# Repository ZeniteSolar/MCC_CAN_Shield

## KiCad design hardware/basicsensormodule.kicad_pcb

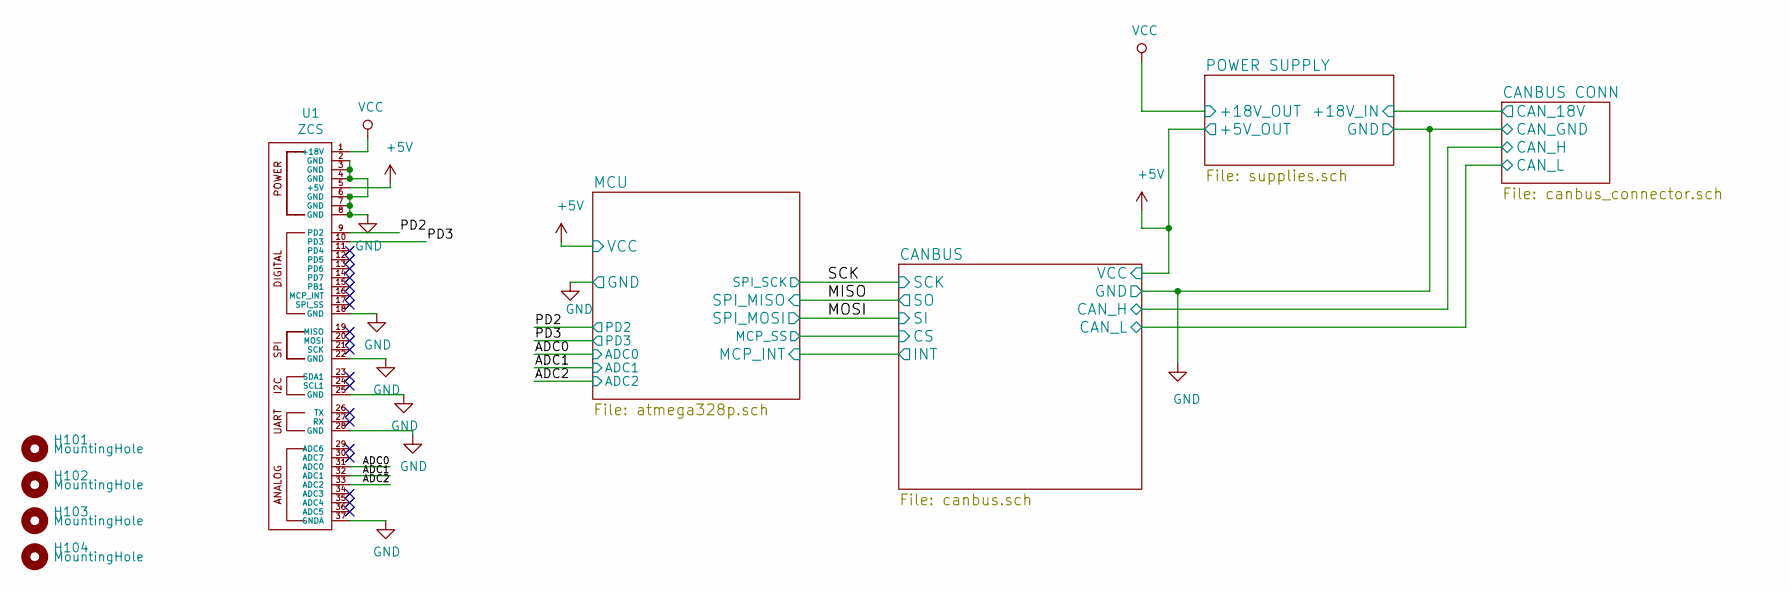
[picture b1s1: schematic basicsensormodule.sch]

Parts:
H101, H102, H103, H104: MountingHole; MountingHole_3.2mm_M3
U1: ZCS; ZCS18

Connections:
+5V: U1.5 (+5V); also elsewhere on the board
/ADC0: U1.31 (ADC0); also elsewhere on the board
/ADC1: U1.32 (ADC1); also elsewhere on the board
/ADC2: U1.33 (ADC2); also elsewhere on the board
/PD2: U1.9 (PD2); also elsewhere on the board
/PD3: U1.10 (PD3); also elsewhere on the board
GND: U1.2 (GND), U1.3 (GND), U1.4 (GND), U1.6 (GND), U1.7 (GND), U1.8 (GND), U1.18 (GND), U1.22 (GND), U1.25 (GND), U1.28 (GND), U1.37 (GNDA); also elsewhere on the board
VCC: U1.1 (+18V); also elsewhere on the board

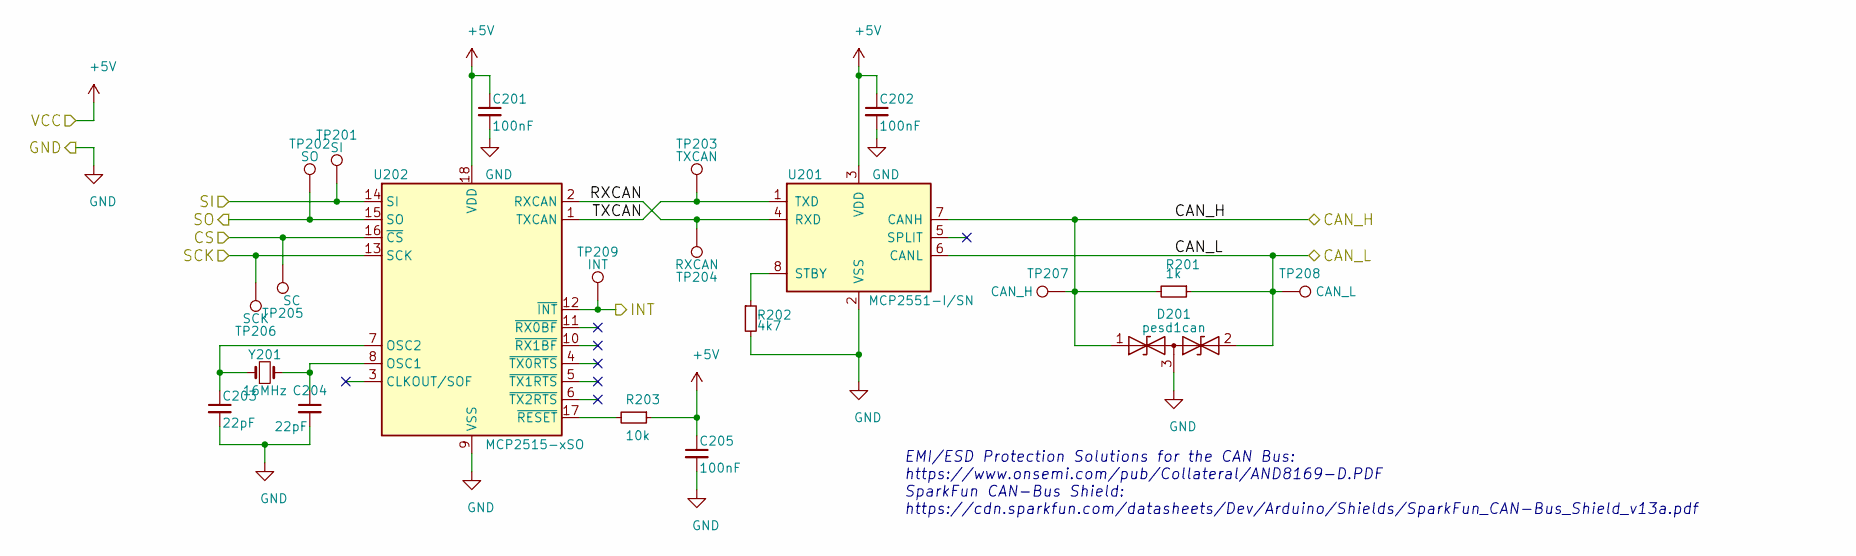
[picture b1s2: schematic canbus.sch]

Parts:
C201, C202, C205: 100nF; C_0805_2012Metric_Pad1.15x1.40mm_HandSolder
C203, C204: 22pF; C_0805_2012Metric_Pad1.15x1.40mm_HandSolder
D201: pesd1can; SOT-23_Handsoldering
R201: 1k; R_0805_2012Metric_Pad1.15x1.40mm_HandSolder
R202: 4k7; R_0805_2012Metric_Pad1.15x1.40mm_HandSolder
R203: 10k; R_0805_2012Metric_Pad1.15x1.40mm_HandSolder
TP201: SI; TestPoint_Pad_2.0x2.0mm
TP202: SO; TestPoint_Pad_2.0x2.0mm
TP203: TXCAN; TestPoint_Pad_2.0x2.0mm
TP204: RXCAN; TestPoint_Pad_2.0x2.0mm
TP205: SC; TestPoint_Pad_2.0x2.0mm
TP206: SCK; TestPoint_Pad_2.0x2.0mm
TP207: CAN_H; TestPoint_Pad_2.0x2.0mm
TP208: CAN_L; TestPoint_Pad_2.0x2.0mm
TP209: INT; TestPoint_Pad_2.0x2.0mm
U201: MCP2551-I/SN; SOIC-8_3.9x4.9mm_P1.27mm
U202: MCP2515-xSO; SOIC-18W_7.5x11.6mm_P1.27mm
Y201: 16MHz; Crystal_HC49-U_Vertical

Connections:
+5V: C201.1, C202.1, C205.1, R203.1, U201.3 (VDD), U202.18 (VDD); also elsewhere on the board
/CANBUS CONN/CAN_H: D201.1 (A1), R201.2, TP207.1, U201.7 (CANH); also elsewhere on the board
/CANBUS CONN/CAN_L: D201.2 (A2), R201.1, TP208.1, U201.6 (CANL); also elsewhere on the board
/CANBUS/CS: TP205.1, U202.16 (~CS); also elsewhere on the board
/CANBUS/INT: TP209.1, U202.12 (~INT); also elsewhere on the board
/CANBUS/RXCAN: TP204.1, U201.4 (RXD), U202.2 (RXCAN)
/CANBUS/TXCAN: TP203.1, U201.1 (TXD), U202.1 (TXCAN)
/MISO: TP202.1, U202.15 (SO); also elsewhere on the board
/MOSI: TP201.1, U202.14 (SI); also elsewhere on the board
/SCK: TP206.1, U202.13 (SCK); also elsewhere on the board
GND: C201.2, C202.2, C203.2, C204.2, C205.2, D201.3 (common), R202.2, U201.2 (VSS), U202.9 (VSS); also elsewhere on the board
unnamed: C203.1, U202.7 (OSC2), Y201.1
unnamed: C204.1, U202.8 (OSC1), Y201.2
unnamed: R202.1, U201.8 (STBY)
unnamed: R203.2, U202.17 (~RESET)

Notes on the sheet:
EMI/ESD Protection Solutions for the CAN Bus: https://www.onsemi.com/pub/Collateral/AND8169-D.PDF SparkFun CAN-Bus Shield: https://cdn.sparkfun.com/datasheets/Dev/Arduino/Shields/SparkFun_CAN-Bus_Shield_v13a.pdf

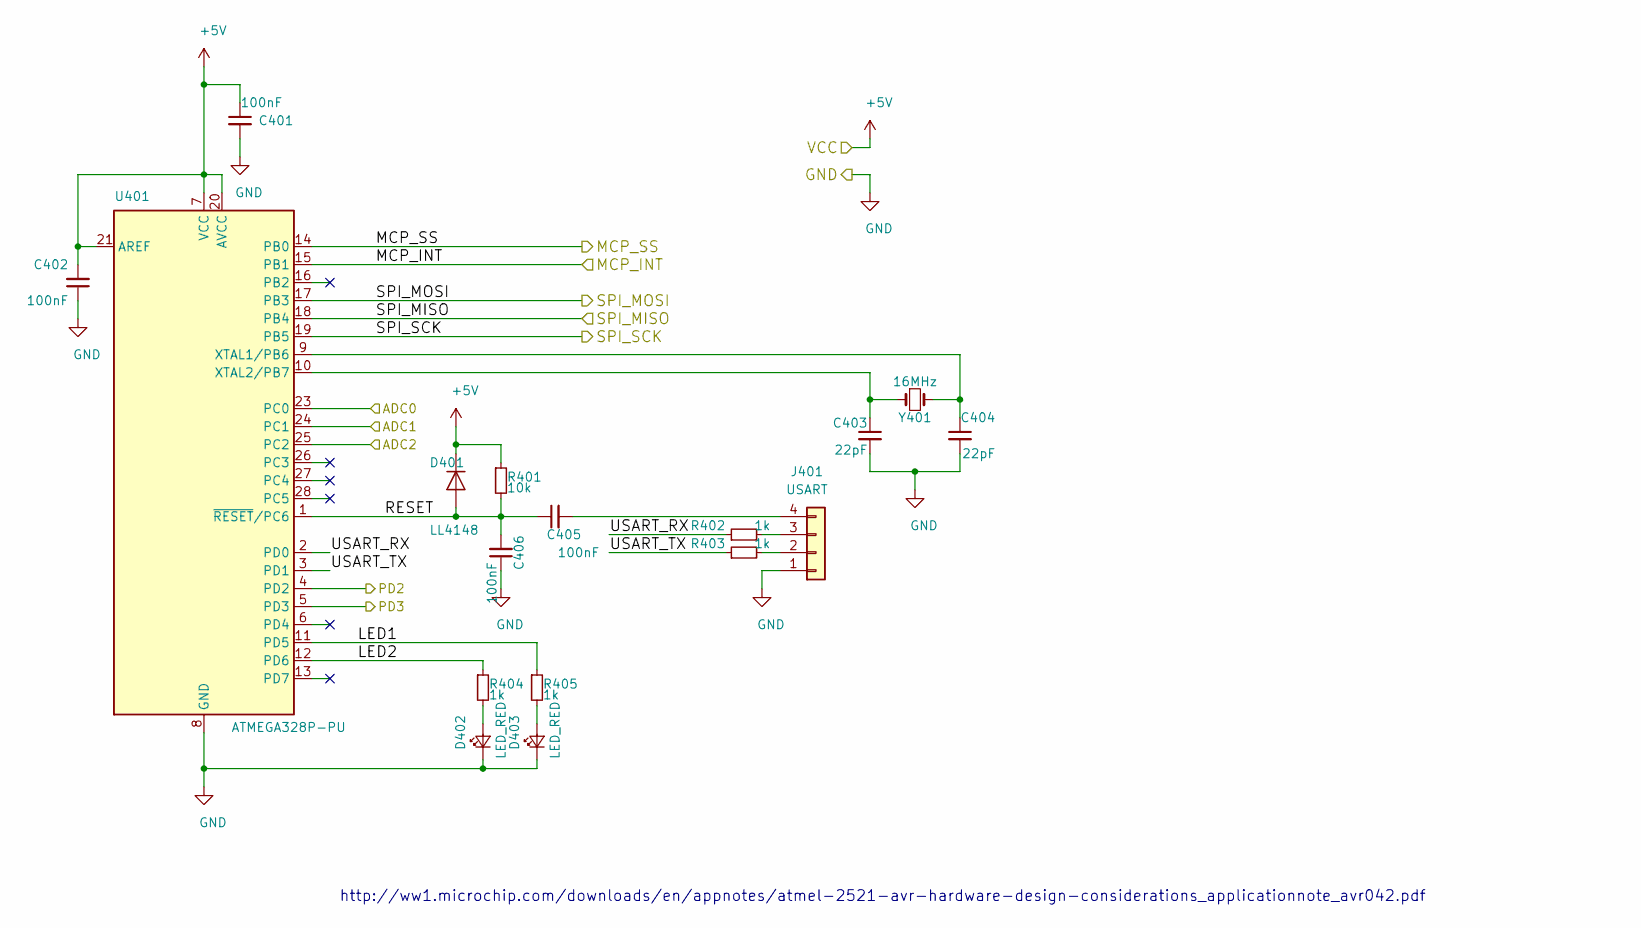
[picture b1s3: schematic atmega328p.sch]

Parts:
C401, C402, C405, C406: 100nF; C_0805_2012Metric_Pad1.15x1.40mm_HandSolder
C403, C404: 22pF; C_0805_2012Metric_Pad1.15x1.40mm_HandSolder
D401: LL4148; D_MiniMELF_Handsoldering
D402, D403: LED_RED; LED_0805_2012Metric_Pad1.15x1.40mm_HandSolder
J401: USART; PinHeader_1x04_P2.54mm_Vertical
R401: 10k; R_0805_2012Metric_Pad1.15x1.40mm_HandSolder
R402, R403, R404, R405: 1k; R_0805_2012Metric_Pad1.15x1.40mm_HandSolder
U401: ATMEGA328P-PU; DIP-28_W7.62mm_Socket
Y401: 16MHz; Crystal_HC49-U_Vertical

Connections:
+5V: C401.1, C402.2, D401.1 (K), R401.1, U401.7 (VCC), U401.20 (AVCC), U401.21 (AREF); also elsewhere on the board
/ADC0: U401.23 (PC0); also elsewhere on the board
/ADC1: U401.24 (PC1); also elsewhere on the board
/ADC2: U401.25 (PC2); also elsewhere on the board
/CANBUS/CS: U401.14 (PB0); also elsewhere on the board
/CANBUS/INT: U401.15 (PB1); also elsewhere on the board
/MCU/LED1: R405.1, U401.11 (PD5)
/MCU/LED2: R404.1, U401.12 (PD6)
/MCU/RESET: C405.1, C406.2, D401.2 (A), R401.2, U401.1 (~RESET~/PC6)
/MCU/USART_RX: R402.1, U401.2 (PD0)
/MCU/USART_TX: R403.1, U401.3 (PD1)
/MISO: U401.18 (PB4); also elsewhere on the board
/MOSI: U401.17 (PB3); also elsewhere on the board
/PD2: U401.4 (PD2); also elsewhere on the board
/PD3: U401.5 (PD3); also elsewhere on the board
/SCK: U401.19 (PB5); also elsewhere on the board
GND: C401.2, C402.1, C403.2, C404.2, C406.1, D402.1 (K), D403.1 (K), J401.1, U401.8 (GND), U401.22 (GND); also elsewhere on the board
unnamed: C403.1, U401.10 (XTAL2/PB7), Y401.1
unnamed: C404.1, U401.9 (XTAL1/PB6), Y401.2
unnamed: C405.2, J401.4
unnamed: D402.2 (A), R404.2
unnamed: D403.2 (A), R405.2
unnamed: J401.2, R403.2
unnamed: J401.3, R402.2

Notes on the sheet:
http://ww1.microchip.com/downloads/en/appnotes/atmel-2521-avr-hardware-design-considerations_applicationnote_avr042.pdf

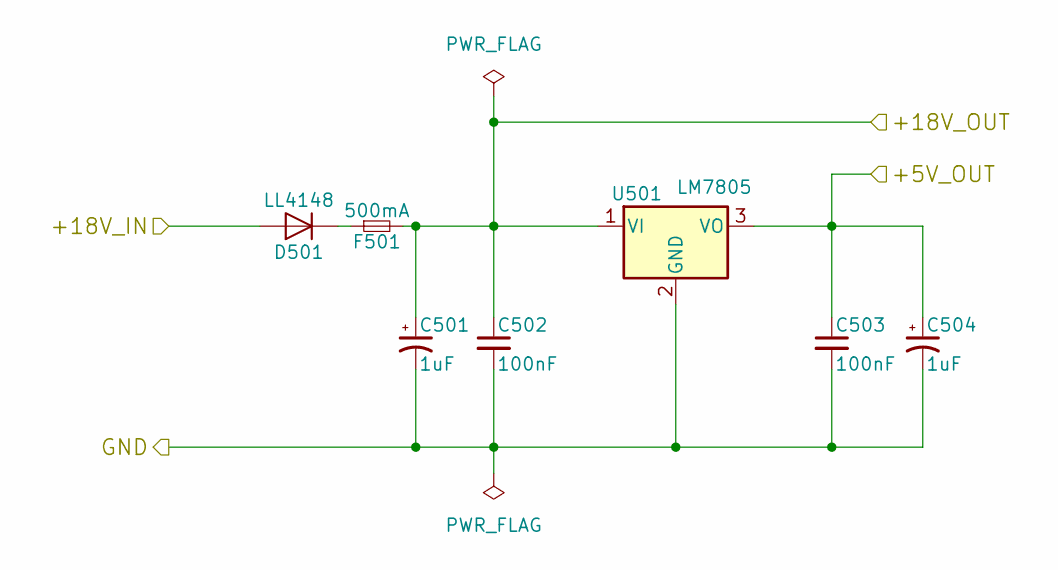
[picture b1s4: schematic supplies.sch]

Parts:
C501, C504: 1uF; CP_EIA-6032-20_AVX-F_Pad2.25x2.35mm_HandSolder
C502, C503: 100nF; C_0805_2012Metric_Pad1.15x1.40mm_HandSolder
D501: LL4148; D_MiniMELF_Handsoldering
F501: 500mA; Fuse_1206_3216Metric_Pad1.42x1.75mm_HandSolder
U501: LM7805; TO-220-3_Horizontal_TabDown_SMD

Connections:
+5V: C503.1, C504.1, U501.3 (VO); also elsewhere on the board
/POWER SUPPLY/+18V_IN: D501.2 (A); also elsewhere on the board
GND: C501.2, C502.2, C503.2, C504.2, U501.2 (GND); also elsewhere on the board
unnamed: D501.1 (K), F501.1
VCC: C501.1, C502.1, F501.2, U501.1 (VI); also elsewhere on the board

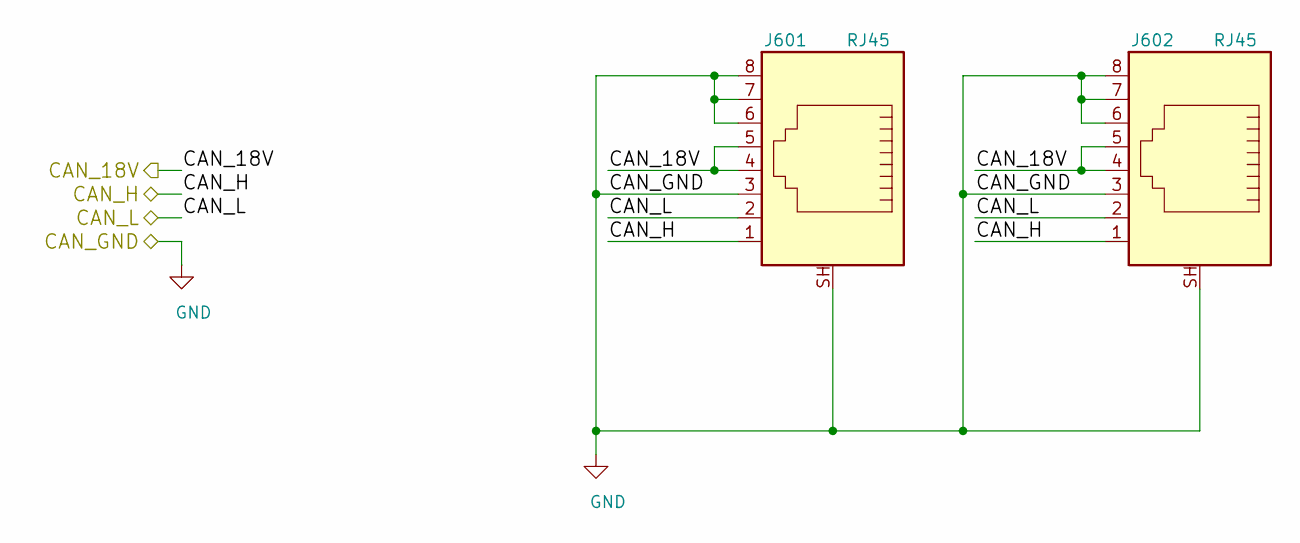
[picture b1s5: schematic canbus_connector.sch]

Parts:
J601, J602: RJ45; RJ45_YH59_01

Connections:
/CANBUS CONN/CAN_H: J601.1, J602.1; also elsewhere on the board
/CANBUS CONN/CAN_L: J601.2, J602.2; also elsewhere on the board
/POWER SUPPLY/+18V_IN: J601.4, J601.5, J602.4, J602.5; also elsewhere on the board
GND: J601.3, J601.6, J601.7, J601.8, J601.SH, J602.3, J602.6, J602.7, J602.8, J602.SH; also elsewhere on the board

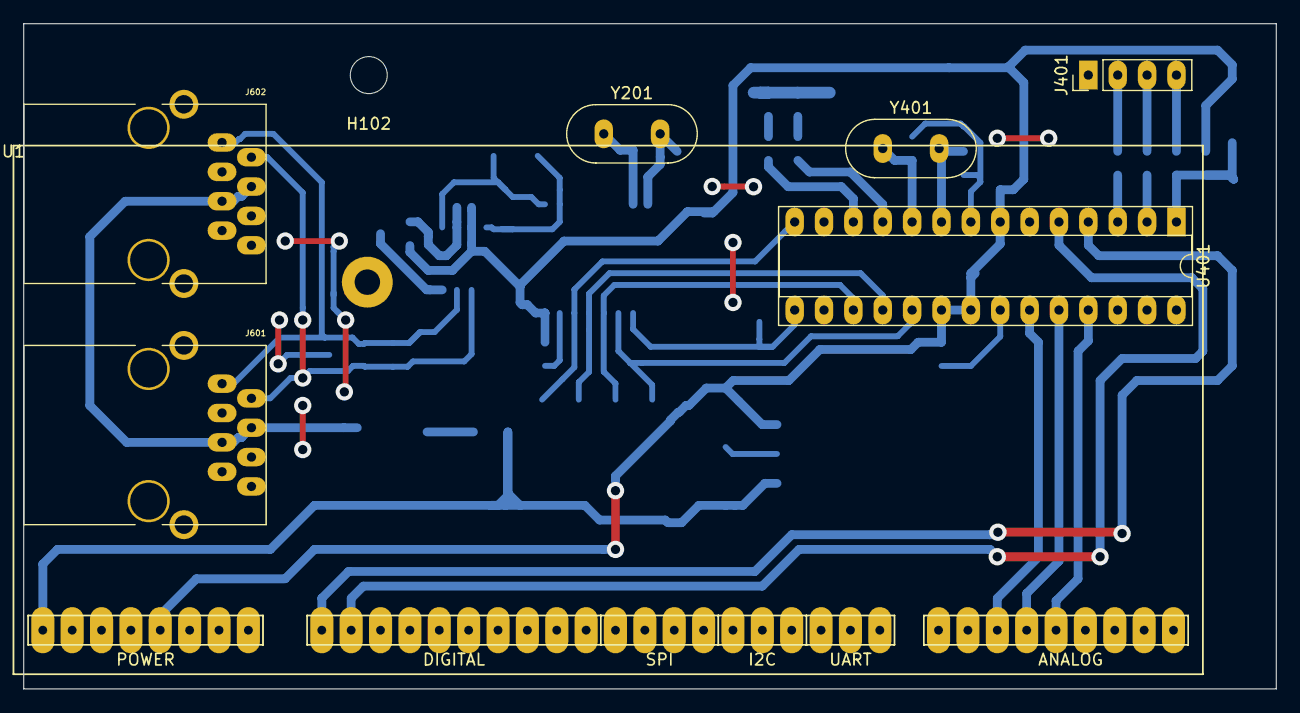
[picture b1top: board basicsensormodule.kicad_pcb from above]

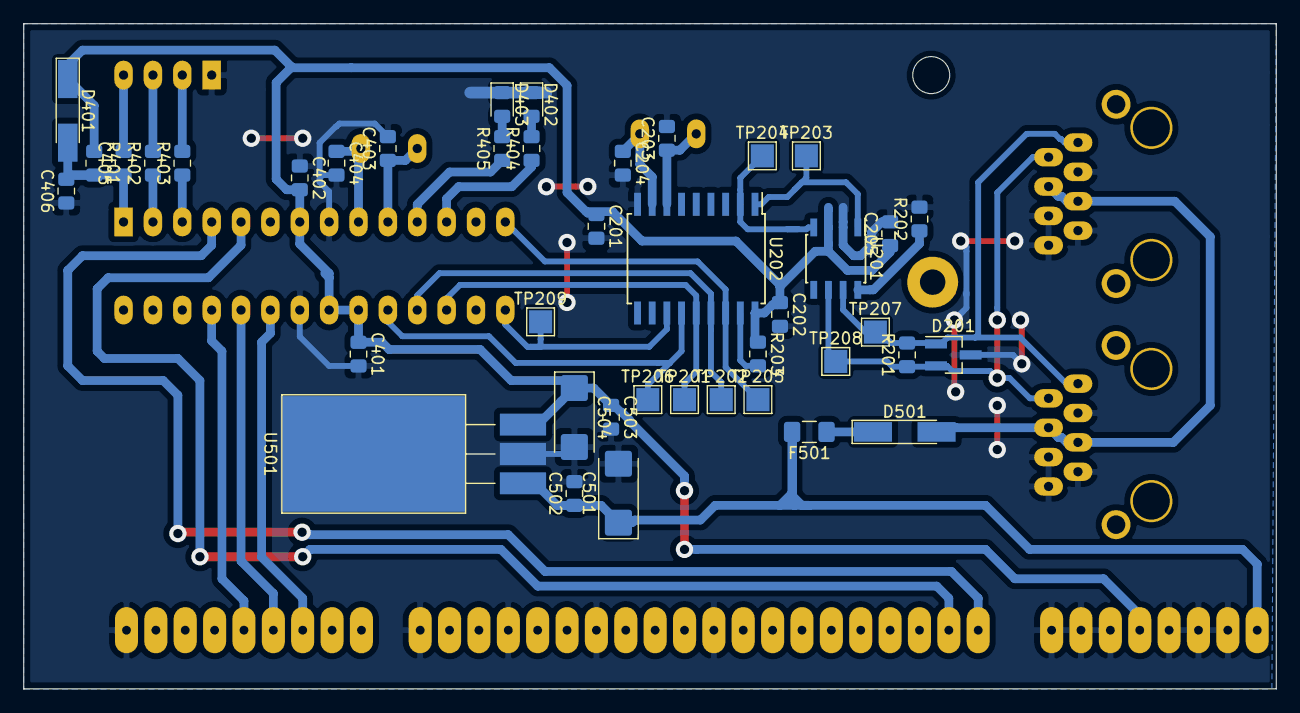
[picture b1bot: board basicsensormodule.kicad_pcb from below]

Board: 2 copper layers, 108.3 x 57.5 mm, 49 parts (41 on the bottom side), 35 nets.

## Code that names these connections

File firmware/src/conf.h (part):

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#define     BatOverVoltageInterrupt_PORT PORTD
#define     BatOverVoltageInterrupt_PIN  PIND
#define     BatOverVoltageInterrupt_DDR  DDRD
#define     BatOverVoltageInterrupt      PD2
#endif // ENABLE_HARDWARE_OVERVOLTAGE_INTERRUPT

#ifdef ENABLE_HARDWARE_ENABLE_SWITCH_INTERRUPT
#define     Enable_PORT             PORTD
#define     Enable_PIN              PIND
#define     Enable_DDR              DDRD
#define     Enable                  PD3
#endif // ENABLE_HARDWARE_ENABLE_SWITCH_INTERRUPT


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#define     LED_PORT                PORTD
#define     LED_PIN                 PIND
#define     LED_DDR                 DDRD
#define     LED1                    PD5
#define     LED2                    PD6
#define     cpl_led(x)               cpl_bit(LED_PORT, x)
#define     set_led(x)               set_bit(LED_PORT, x)
#define     clr_led(x)               clr_bit(LED_PORT, x)
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
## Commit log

2020-01-23 tudo
2020-01-25 WARNING
2020-01-26 firmware with cascade pi controller for input
2020-01-26 saving closed loop PI controllers for future usage
2020-01-26 MPPT working again.
2020-01-26 small bug fixed
2020-02-02 last version from DSB20 SFS
2021-12-09 Use default system-wide avr-gcc toolchain
2021-12-09 Ignore can_ids.h
2021-12-09 Use extern modifier to fix duplicated variables being defined on newer GCC
2022-03-19 makefile: Add several compiler flags, change optimization to 's', use system installed avr-gcc.
2022-10-06 add power limit algorith (without testing)
2022-10-06 do a sweep when current is under 100mA
2023-06-01 use can ids frequency, and fix frequency computation
